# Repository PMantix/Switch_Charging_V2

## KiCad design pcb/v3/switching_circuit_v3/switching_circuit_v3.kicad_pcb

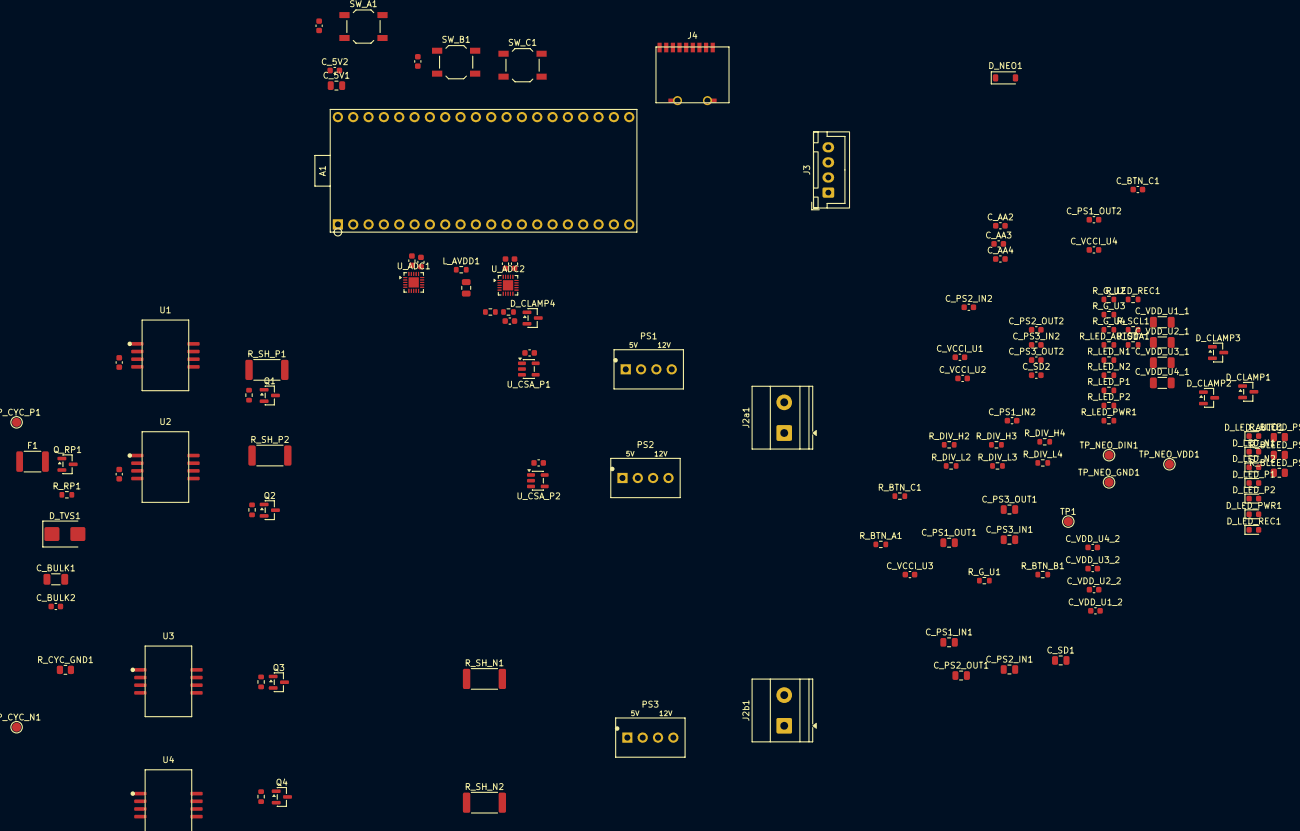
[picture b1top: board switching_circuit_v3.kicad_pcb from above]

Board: 2 copper layers, 128 parts (0 on the bottom side), 70 nets, no tracks yet.

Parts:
A1: Pico2; Pico2_SocketedTH
C_5V1: 10uF; C_0805_2012Metric
C_5V2: 100nF; C_0603_1608Metric
C_AA1, C_AA2, C_AA3, C_AA4: 100nF; C_0603_1608Metric
C_AVDD1: 10uF; C_0805_2012Metric
C_AVDD2_U1, C_AVDD2_U2: 100nF; C_0603_1608Metric
C_BTN_A1: 100nF; C_0603_1608Metric
C_BTN_B1: 100nF; C_0603_1608Metric
C_BTN_C1: 100nF; C_0603_1608Metric
C_BULK1: 10uF; C_1206_3216Metric
C_BULK2: 100nF; C_0603_1608Metric
C_CAP_U1, C_CAP_U2: 220nF; C_0603_1608Metric
C_CSA_P1, C_CSA_P2: 100nF; C_0603_1608Metric
C_DVDD_U1, C_DVDD_U2: 1uF; C_0603_1608Metric
C_PS1_IN1, C_PS2_IN1, C_PS3_IN1: 4.7uF; C_0805_2012Metric
C_PS1_IN2, C_PS1_OUT2, C_PS2_IN2, C_PS2_OUT2, C_PS3_IN2, C_PS3_OUT2: 100nF; C_0603_1608Metric
C_PS1_OUT1, C_PS2_OUT1, C_PS3_OUT1: 2.2uF; C_0805_2012Metric
C_SD1: 10uF; C_0805_2012Metric
C_SD2: 100nF; C_0603_1608Metric
C_VCCI_U1, C_VCCI_U2, C_VCCI_U3, C_VCCI_U4: 100nF; C_0603_1608Metric
C_VDD_U1_1, C_VDD_U2_1, C_VDD_U3_1, C_VDD_U4_1: 10uF; C_1206_3216Metric
C_VDD_U1_2, C_VDD_U2_2, C_VDD_U3_2, C_VDD_U4_2: 100nF; C_0603_1608Metric
D_CLAMP1, D_CLAMP2, D_CLAMP3, D_CLAMP4: BAV99; SOT-23
D_LED_AUTO1: YELLOW; LED_0603_1608Metric
D_LED_N1, D_LED_N2: GREEN; LED_0603_1608Metric
D_LED_P1, D_LED_P2: GREEN; LED_0603_1608Metric
D_LED_PWR1: GREEN; LED_0603_1608Metric
D_LED_REC1: GREEN; LED_0603_1608Metric
D_NEO1: 1N4148W; D_SOD-123
D_TVS1: SMBJ12CA; D_SMB
F1: 3A; Fuse_1812_4532Metric
J2a1: Cell+; TerminalBlock_Phoenix_MKDS-1,5-2-5.08_1x02_P5.08mm_Horizont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
J2b1: Cell-; TerminalBlock_Phoenix_MKDS-1,5-2-5.08_1x02_P5.08mm_Horizont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
J3: OLED; JST_XH_B4B-XH-A_1x04_P2.50mm_Vertical
J4: microSD; TF_PUSH
L_AVDD1: 600R@100MHz; R_0603_1608Metric
PS1, PS2, PS3: B0512S-1WR3; B0512S_1WR3_SIP4
Q1, Q2, Q3, Q4: AO3400A; SOT-23
Q_RP1: AO3401A; SOT-23
R_BLEED_PS1, R_BLEED_PS2, R_BLEED_PS3: 1.2k; R_0805_2012Metric
R_BTN_A1: 10k; R_0603_1608Metric
R_BTN_B1: 10k; R_0603_1608Metric
R_BTN_C1: 10k; R_0603_1608Metric
R_CYC_GND1: 0R; R_0805_2012Metric
R_DIV_H1, R_DIV_H2, R_DIV_H3, R_DIV_H4: 91k; R_0603_1608Metric
R_DIV_L1, R_DIV_L2, R_DIV_L3, R_DIV_L4: 9.1k; R_0603_1608Metric
R_G_U1, R_G_U2, R_G_U3, R_G_U4: 10R; R_0603_1608Metric
R_LED_AUTO1: 1k; R_0603_1608Metric
R_LED_N1, R_LED_N2: 1k; R_0603_1608Metric
R_LED_P1, R_LED_P2: 1k; R_0603_1608Metric
R_LED_PWR1: 1k; R_0603_1608Metric
R_LED_REC1: 1k; R_0603_1608Metric
R_RP1: 10k; R_0603_1608Metric
R_SCL1: 4.7k; R_0603_1608Metric
R_SDA1: 4.7k; R_0603_1608Metric
R_SH_N1, R_SH_N2: 0R01; R_2512_6332Metric
R_SH_P1, R_SH_P2: 0R01; R_2512_6332Metric
Rgpd_1, Rgpd_2, Rgpd_3, Rgpd_4: 10k; R_0603_1608Metric
SW_A1: SW; SW_SPST_TL3342
SW_B1: SW; SW_SPST_TL3342
SW_C1: SW; SW_SPST_TL3342
TP1: GP28; TestPoint_Pad_D1.5mm
TP_CYC_N1: CYCLER_IN-; TestPoint_Pad_D1.5mm
TP_CYC_P1: CYCLER_IN+; TestPoint_Pad_D1.5mm
TP_NEO_DIN1: NEO_DIN; TestPoint_Pad_D1.5mm
TP_NEO_GND1: NEO_GND; TestPoint_Pad_D1.5mm
TP_NEO_VDD1: NEO_VDD; TestPoint_Pad_D1.5mm
U1, U2, U3, U4: UCC5304DWVR; SOIC-8_DWV_7.5x11.5mm_P1.27mm
U_ADC1, U_ADC2: ADS131M04; Texas_RUK0020B_WQFN-20-1EP_3x3mm_P0.4mm_EP1.7x1.7mm
U_CSA_P1, U_CSA_P2: INA180A1; SOT-23-5

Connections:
+3V3: A1.3V3_OUT, C_CSA_P1.1, C_CSA_P2.1, C_DVDD_U1.1, C_DVDD_U2.1, C_SD1.1, C_SD2.1, C_VCCI_U1.1, C_VCCI_U2.1, C_VCCI_U3.1, C_VCCI_U4.1, D_LED_N1.2 (A), D_LED_N2.2 (A), D_LED_P1.2 (A), D_LED_P2.2 (A), D_LED_PWR1.2 (A), J3.1, J4.5, L_AVDD1.1, R_BTN_A1.1, R_BTN_B1.1, R_BTN_C1.1, R_SCL1.1, R_SDA1.1, U1.2 (VCCI), U1.3 (VCCI), U2.2 (VCCI), U2.3 (VCCI), U3.2 (VCCI), U3.3 (VCCI), U4.2 (VCCI), U4.3 (VCCI), U_ADC1.18 (DVDD), U_ADC2.18 (DVDD), U_CSA_P1.5 (VS), U_CSA_P2.5 (VS)
+3V3_A: C_AVDD1.1, C_AVDD2_U1.1, C_AVDD2_U2.1, D_CLAMP1.2 (S), D_CLAMP2.2 (S), D_CLAMP3.2 (S), D_CLAMP4.2 (S), L_AVDD1.2, U_ADC1.19 (AVDD), U_ADC2.19 (AVDD)
+5V: A1.VBUS, C_5V1.1, C_5V2.1, C_PS1_IN1.1, C_PS1_IN2.1, C_PS2_IN1.1, C_PS2_IN2.1, C_PS3_IN1.1, C_PS3_IN2.1, D_NEO1.2 (A), PS1.2 (Vin+), PS2.2 (Vin+), PS3.2 (Vin+)
+HV: C_BULK1.1, C_BULK2.1, D_TVS1.2 (A2), Q_RP1.3 (D), R_DIV_H1.1, R_SH_P1.1, R_SH_P2.1, U_CSA_P1.3 (IN+), U_CSA_P2.3 (IN+)
+HV_P1: Q1.3 (D), R_DIV_H2.1, R_SH_P1.2, U_CSA_P1.4 (IN-)
+HV_P2: Q2.3 (D), R_DIV_H3.1, R_SH_P2.2, U_CSA_P2.4 (IN-)
+HV_PREFUSE: F1.2, Q_RP1.2 (S), R_RP1.1
ADS1_CS: A1.GP13, U_ADC1.10 (CS)
ADS1_DRDY: A1.GP14, U_ADC1.11 (DRDY)
ADS2_CS: A1.GP26, U_ADC2.10 (CS)
ADS2_DRDY: A1.GP21, U_ADC2.11 (DRDY)
ADS_CLKIN: A1.GP27, U_ADC1.15 (CLKIN), U_ADC2.15 (CLKIN)
ADS_MISO: A1.GP12, U_ADC1.13 (DOUT), U_ADC2.13 (DOUT)
ADS_MOSI: A1.GP11, U_ADC1.14 (DIN), U_ADC2.14 (DIN)
ADS_RESET: A1.GP15, U_ADC1.9 (SYNC/RESET), U_ADC2.9 (SYNC/RESET)
ADS_SCK: A1.GP10, U_ADC1.12 (SCLK), U_ADC2.12 (SCLK)
AGND: A1.AGND, C_AA1.2, C_AA2.2, C_AA3.2, C_AA4.2, C_AVDD1.2, C_AVDD2_U1.2, C_AVDD2_U2.2, D_CLAMP1.1 (G), D_CLAMP2.1 (G), D_CLAMP3.1 (G), D_CLAMP4.1 (G), R_DIV_L1.2, R_DIV_L2.2, R_DIV_L3.2, R_DIV_L4.2, U_ADC1.2 (AIN0N), U_ADC1.3 (AIN1N), U_ADC1.20 (AGND), U_ADC1.21 (EPAD), U_ADC2.2 (AIN0N), U_ADC2.3 (AIN1N), U_ADC2.6 (AIN2N), U_ADC2.7 (AIN3N), U_ADC2.20 (AGND), U_ADC2.21 (EPAD)
BTN_A: A1.GP8, C_BTN_A1.1, R_BTN_A1.2, SW_A1.1
BTN_B: A1.GP9, C_BTN_B1.1, R_BTN_B1.2, SW_B1.1
BTN_C: A1.GP20, C_BTN_C1.1, R_BTN_C1.2, SW_C1.1
CAP1: C_CAP_U1.1, U_ADC1.16 (CAP)
CAP2: C_CAP_U2.1, U_ADC2.16 (CAP)
CELL_A_NEG: J2b1.1, Q3.3 (D)
CELL_A_POS: C_PS1_OUT1.2, C_PS1_OUT2.2, C_VDD_U1_1.2, C_VDD_U1_2.2, J2a1.1, PS1.3 (Vout-), Q1.2 (S), R_BLEED_PS1.2, Rgpd_1.2, U1.5 (VSS), U1.6 (VSS)
CELL_B_NEG: J2b1.2, Q4.3 (D)
CELL_B_POS: C_PS2_OUT1.2, C_PS2_OUT2.2, C_VDD_U2_1.2, C_VDD_U2_2.2, J2a1.2, PS2.3 (Vout-), Q2.2 (S), R_BLEED_PS2.2, Rgpd_2.2, U2.5 (VSS), U2.6 (VSS)
CSA_P1_OUT: U_ADC1.1 (AIN0P), U_CSA_P1.1 (OUT)
CSA_P2_OUT: U_ADC1.4 (AIN1P), U_CSA_P2.1 (OUT)
CYCLER_IN+: F1.1, TP_CYC_P1.1 (1_1)
CYCLER_IN-: Q_RP1.1 (G), R_CYC_GND1.1, R_RP1.2, TP_CYC_N1.1 (1_1)
D_LED_N1_K: D_LED_N1.1 (K), R_LED_N1.1
D_LED_N2_K: D_LED_N2.1 (K), R_LED_N2.1
D_LED_P1_K: D_LED_P1.1 (K), R_LED_P1.1
D_LED_P2_K: D_LED_P2.1 (K), R_LED_P2.1
GATE_N1_IN: A1.GP4, R_LED_N1.2, U3.1 (IN)
GATE_N1_OUT: Q3.1 (G), R_G_U3.2, Rgpd_3.1
GATE_N1_OUT_PRE: R_G_U3.1, U3.7 (OUT)
GATE_N2_IN: A1.GP5, R_LED_N2.2, U4.1 (IN)
GATE_N2_OUT: Q4.1 (G), R_G_U4.2, Rgpd_4.1
GATE_N2_OUT_PRE: R_G_U4.1, U4.7 (OUT)
GATE_P1_IN: A1.GP2, R_LED_P1.2, U1.1 (IN)
GATE_P1_OUT: Q1.1 (G), R_G_U1.2, Rgpd_1.1
GATE_P1_OUT_PRE: R_G_U1.1, U1.7 (OUT)
GATE_P2_IN: A1.GP3, R_LED_P2.2, U2.1 (IN)
GATE_P2_OUT: Q2.1 (G), R_G_U2.2, Rgpd_2.1
GATE_P2_OUT_PRE: R_G_U2.1, U2.7 (OUT)
GND: A1.GND1 (GND), A1.GND2 (GND), C_5V1.2, C_5V2.2, C_BTN_A1.2, C_BTN_B1.2, C_BTN_C1.2, C_BULK1.2, C_BULK2.2, C_CAP_U1.2, C_CAP_U2.2, C_CSA_P1.2, C_CSA_P2.2, C_DVDD_U1.2, C_DVDD_U2.2, C_PS1_IN1.2, C_PS1_IN2.2, C_PS2_IN1.2, C_PS2_IN2.2, C_PS3_IN1.2, C_PS3_IN2.2, C_PS3_OUT1.2, C_PS3_OUT2.2, C_SD1.2, C_SD2.2, C_VCCI_U1.2, C_VCCI_U2.2, C_VCCI_U3.2, C_VCCI_U4.2, C_VDD_U3_1.2, C_VDD_U3_2.2, C_VDD_U4_1.2, C_VDD_U4_2.2, D_LED_AUTO1.1 (K), D_LED_REC1.1 (K), D_TVS1.1 (A1), J3.2, J4.6, PS1.1 (Vin-), PS2.1 (Vin-), PS3.1 (Vin-), PS3.3 (Vout-), R_BLEED_PS3.2, R_CYC_GND1.2, R_LED_PWR1.2, R_SH_N1.2, R_SH_N2.2, SW_A1.2, SW_B1.2, SW_C1.2, TP_NEO_GND1.1 (1_1), U1.4 (GND), U2.4 (GND), U3.4 (GND), U3.5 (VSS), U3.6 (VSS), U4.4 (GND), U4.5 (VSS), U4.6 (VSS), U_ADC1.6 (AIN2N), U_ADC1.7 (AIN3N), U_ADC1.17 (DGND), U_ADC2.17 (DGND), U_CSA_P1.2 (GND), U_CSA_P2.2 (GND)
GND_N1: Q3.2 (S), R_DIV_H4.1, R_SH_N1.1, Rgpd_3.2, U_ADC1.5 (AIN2P)
GND_N2: Q4.2 (S), R_SH_N2.1, Rgpd_4.2, U_ADC1.8 (AIN3P)
LED_AUTO: A1.GP0, R_LED_AUTO1.2
LED_AUTO_A: D_LED_AUTO1.2 (A), R_LED_AUTO1.1
LED_REC: A1.GP22, R_LED_REC1.2
LED_REC_A: D_LED_REC1.2 (A), R_LED_REC1.1
NEOPIXEL: A1.GP1, TP_NEO_DIN1.1 (1_1)
NEO_VDD: D_NEO1.1 (K), TP_NEO_VDD1.1 (1_1)
PWR_LED_K: D_LED_PWR1.1 (K), R_LED_PWR1.1
SCL: A1.GP7, J3.4, R_SCL1.2
SDA: A1.GP6, J3.3, R_SDA1.2
SD_CS: A1.GP17, J4.2
SD_MISO: A1.GP16, J4.1
SD_MOSI: A1.GP19, J4.4
SD_SCK: A1.GP18, J4.3
TP_GP28: A1.GP28, TP1.1 (1_1)
VCC2_LS: C_PS3_OUT1.1, C_PS3_OUT2.1, C_VDD_U3_1.1, C_VDD_U3_2.1, C_VDD_U4_1.1, C_VDD_U4_2.1, PS3.4 (Vout+), R_BLEED_PS3.1, U3.8 (VDD), U4.8 (VDD)
VCC2_P1: C_PS1_OUT1.1, C_PS1_OUT2.1, C_VDD_U1_1.1, C_VDD_U1_2.1, PS1.4 (Vout+), R_BLEED_PS1.1, U1.8 (VDD)
VCC2_P2: C_PS2_OUT1.1, C_PS2_OUT2.1, C_VDD_U2_1.1, C_VDD_U2_2.1, PS2.4 (Vout+), R_BLEED_PS2.1, U2.8 (VDD)
VDIV_GND_N1: C_AA4.1, D_CLAMP4.3 (D), R_DIV_H4.2, R_DIV_L4.1, U_ADC2.8 (AIN3P)
VDIV_HV: C_AA1.1, D_CLAMP1.3 (D), R_DIV_H1.2, R_DIV_L1.1, U_ADC2.1 (AIN0P)
VDIV_HV_P1: C_AA2.1, D_CLAMP2.3 (D), R_DIV_H2.2, R_DIV_L2.1, U_ADC2.4 (AIN1P)
VDIV_HV_P2: C_AA3.1, D_CLAMP3.3 (D), R_DIV_H3.2, R_DIV_L3.1, U_ADC2.5 (AIN2P)

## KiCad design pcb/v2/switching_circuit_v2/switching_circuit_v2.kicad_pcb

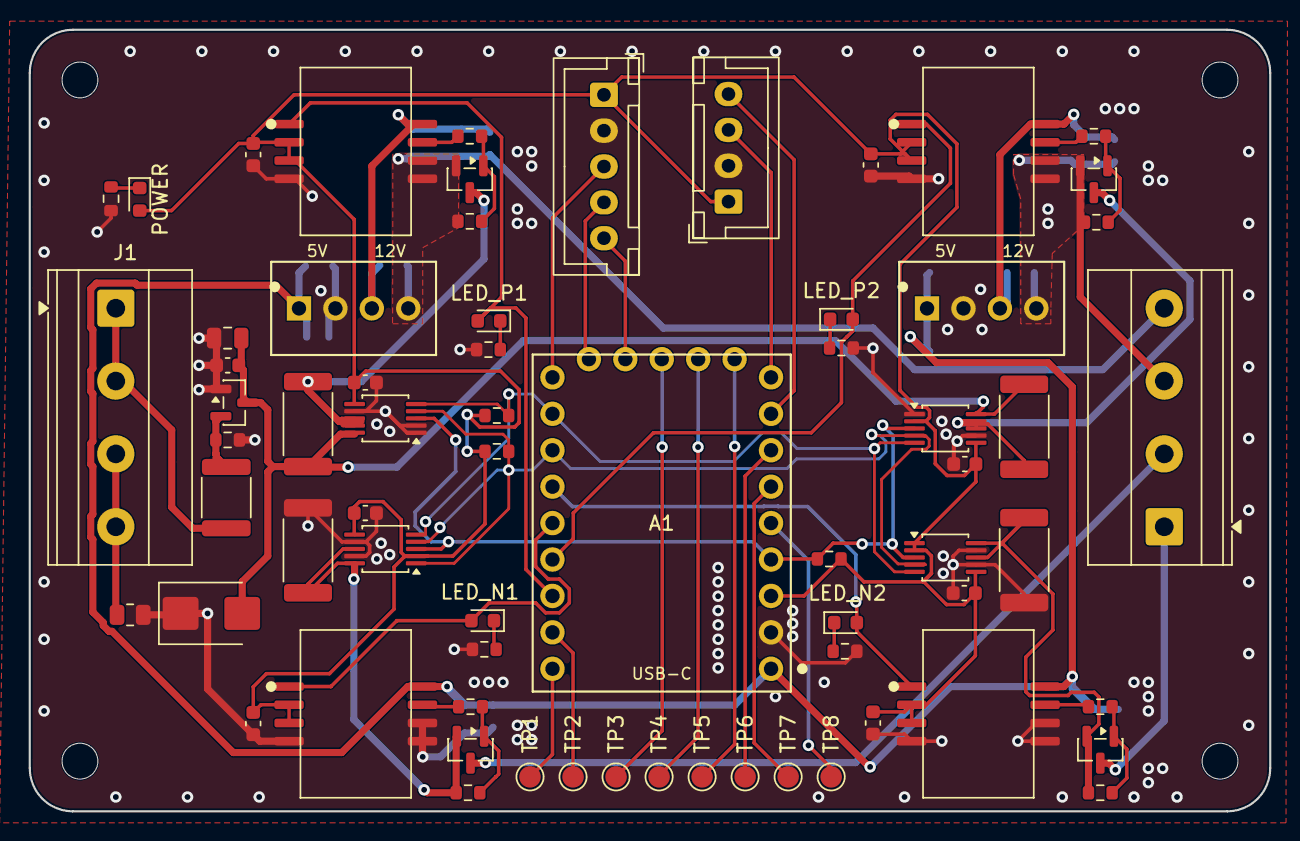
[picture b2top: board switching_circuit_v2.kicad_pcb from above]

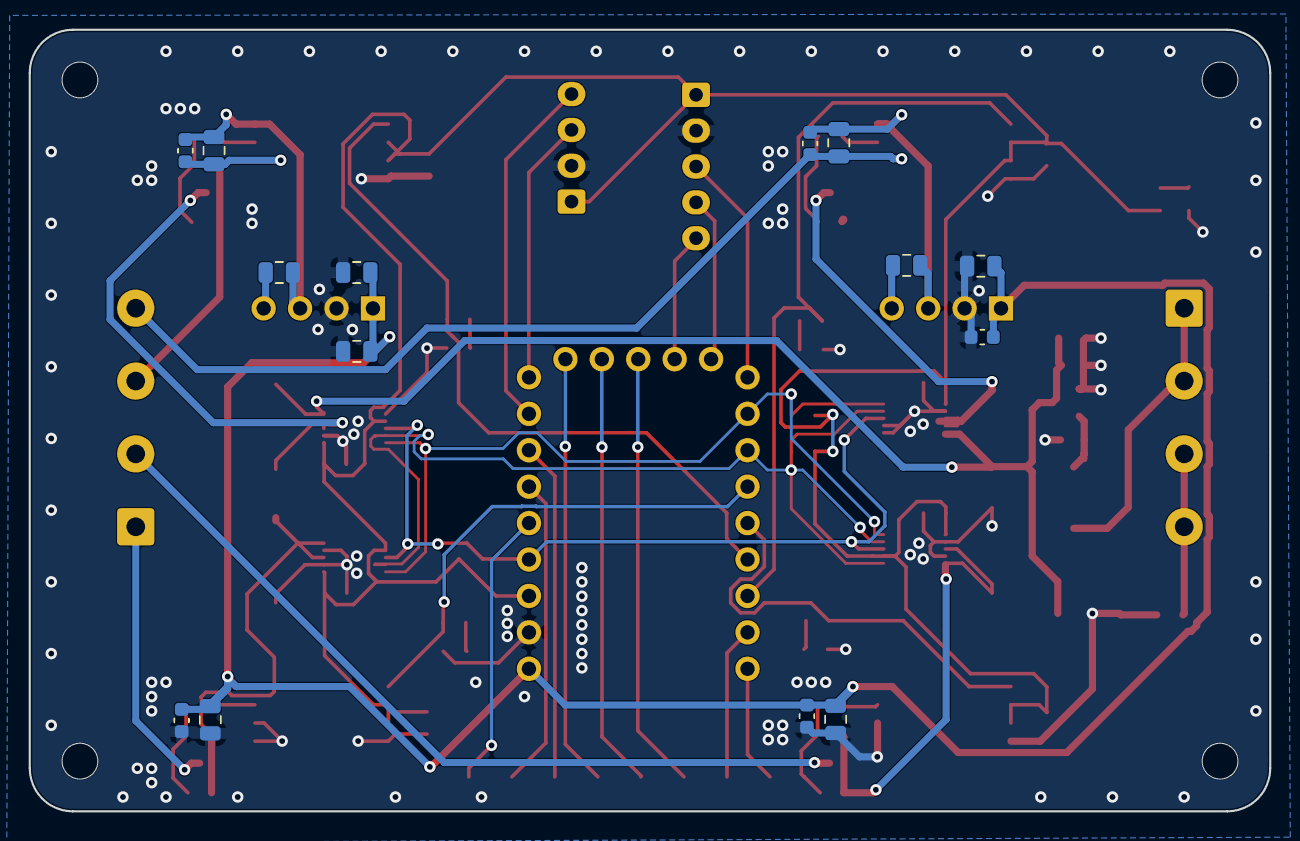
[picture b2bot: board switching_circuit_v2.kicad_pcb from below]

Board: 2 copper layers, 86.5 x 54.5 mm, 81 parts (14 on the bottom side), 50 nets.

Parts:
A1: RP2040-Zero; RP2040_Zero_SocketedTH
C_5V1: 10uF; C_0805_2012Metric
C_5V2: 100nF; C_0603_1608Metric
C_B1: 10uF; C_0805_2012Metric
C_B2: 100nF; C_0603_1608Metric
C_INA_N1, C_INA_N2: 100nF; C_0603_1608Metric
C_INA_P1, C_INA_P2: 100nF; C_0603_1608Metric
C_PS1_IN1, C_PS2_IN1: 4.7uF; C_0805_2012Metric
C_PS1_OUT1, C_PS2_OUT1: 2.2uF; C_0805_2012Metric
C_VCCI_U1, C_VCCI_U2, C_VCCI_U3, C_VCCI_U4: 100nF; C_0603_1608Metric
C_VDD_U1_1, C_VDD_U2_1, C_VDD_U3_1, C_VDD_U4_1: 10uF; C_0805_2012Metric
C_VDD_U1_2, C_VDD_U2_2, C_VDD_U3_2, C_VDD_U4_2: 100nF; C_0603_1608Metric
D_LED_N1: GREEN; LED_0603_1608Metric
D_TVS1: SMBJ12CA; D_SMB
F1: 3A; Fuse_1812_4532Metric
J1: Cycler In; TerminalBlock_Phoenix_MKDS-1,5-4-5.08_1x04_P5.08mm_Horizont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
J2: Cell; TerminalBlock_Phoenix_MKDS-1,5-4-5.08_1x04_P5.08mm_Horizont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
J3: Encoder; JST_XH_B5B-XH-A_1x05_P2.50mm_Vertical
J4: Display; JST_XH_B4B-XH-A_1x04_P2.50mm_Vertical
LED_N1: 1k; R_0603_1608Metric
LED_N2: GREEN; LED_0603_1608Metric
LED_P1, LED_P2: GREEN; LED_0603_1608Metric
POWER: GREEN; LED_0603_1608Metric
PS1, PS2: B0512S-1WR3; B0512S_1WR3_SIP4
Q1, Q2, Q3, Q4: AO3400A; SOT-23
Q_RP1: AO3401A; SOT-23
R_ALERT1: 4.7k; R_0603_1608Metric
R_CYC_GND1: 0R; R_0805_2012Metric
R_G_U1, R_G_U2, R_G_U3, R_G_U4: 10R; R_0603_1608Metric
R_LED_N2: 1k; R_0603_1608Metric
R_LED_P1, R_LED_P2: 1k; R_0603_1608Metric
R_LED_PWR1: 1k; R_0603_1608Metric
R_RP1: 10k; R_0603_1608Metric
R_SCL1: 4.7k; R_0603_1608Metric
R_SDA1: 4.7k; R_0603_1608Metric
R_SH_N1, R_SH_N2: 0R05; R_2512_6332Metric
R_SH_P1, R_SH_P2: 0R05; R_2512_6332Metric
Rgpd_1, Rgpd_2, Rgpd_3, Rgpd_4: 10k; R_0603_1608Metric
TP1: TP TP_GP0; TestPoint_Pad_D1.5mm
TP2: TP TP_GP1; TestPoint_Pad_D1.5mm
TP3: TP TP_GP11; TestPoint_Pad_D1.5mm
TP4: TP TP_GP12; TestPoint_Pad_D1.5mm
TP5: TP TP_GP13; TestPoint_Pad_D1.5mm
TP6: TP TP_GP26; TestPoint_Pad_D1.5mm
TP7: TP TP_GP27; TestPoint_Pad_D1.5mm
TP8: TP TP_GP28; TestPoint_Pad_D1.5mm
U1, U2, U3, U4: UCC5304DWVR; SOIC-8_DWV_7.5x11.5mm_P1.27mm
U_INA_N1, U_INA_N2: INA226; TSSOP-10_3x3mm_P0.5mm
U_INA_P1, U_INA_P2: INA226; TSSOP-10_3x3mm_P0.5mm

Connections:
+3V3: A1.3V3, C_INA_N1.1, C_INA_N2.1, C_INA_P1.1, C_INA_P2.1, C_VCCI_U1.1, C_VCCI_U2.1, C_VCCI_U3.1, C_VCCI_U4.1, J3.1, J4.1, POWER.2 (A), R_ALERT1.1, R_SCL1.1, R_SDA1.1, U1.2 (VCCI), U1.3 (VCCI), U2.2 (VCCI), U2.3 (VCCI), U3.2 (VCCI), U3.3 (VCCI), U4.2 (VCCI), U4.3 (VCCI), U_INA_N1.2 (A0), U_INA_N1.6 (VS), U_INA_N2.1 (A1), U_INA_N2.2 (A0), U_INA_N2.6 (VS), U_INA_P1.6 (VS), U_INA_P2.2 (A0), U_INA_P2.6 (VS)
+5V: A1.5V, C_5V1.1, C_5V2.1, C_PS1_IN1.1, C_PS2_IN1.1, C_VDD_U3_1.1, C_VDD_U3_2.1, C_VDD_U4_1.1, C_VDD_U4_2.1, PS1.1 (Vin+), PS2.1 (Vin+), U3.8 (VDD), U4.8 (VDD)
+HV: C_B1.1, C_B2.1, D_TVS1.2 (A2), Q_RP1.3 (D), R_SH_P1.1, R_SH_P2.1, U_INA_P1.10 (Vin+), U_INA_P2.10 (Vin+)
+HV_P1: Q1.3 (D), R_SH_P1.2, U_INA_P1.8 (Vbus), U_INA_P1.9 (Vin-)
+HV_P2: Q2.3 (D), R_SH_P2.2, U_INA_P2.8 (Vbus), U_INA_P2.9 (Vin-)
+HV_PREFUSE: F1.2, Q_RP1.2 (S), R_RP1.1
ALERT: A1.GP29, R_ALERT1.2, U_INA_N1.3 (~Alert), U_INA_N2.3 (~Alert), U_INA_P1.3 (~Alert), U_INA_P2.3 (~Alert)
CELL_A_NEG: J2.2, Q3.3 (D)
CELL_A_POS: C_PS1_OUT1.2, C_VDD_U1_1.2, C_VDD_U1_2.2, J2.4, PS1.4 (Vout-), Q1.2 (S), Rgpd_1.2, U1.5 (VSS), U1.6 (VSS)
CELL_B_NEG: J2.1, Q4.3 (D)
CELL_B_POS: C_PS2_OUT1.2, C_VDD_U2_1.2, C_VDD_U2_2.2, J2.3, PS2.4 (Vout-), Q2.2 (S), Rgpd_2.2, U2.5 (VSS), U2.6 (VSS)
CYCLER_IN+: F1.1, J1.1, J1.2
CYCLER_IN-: J1.3, J1.4, R_CYC_GND1.1
DISPLAY_CLK: A1.GP14, J4.3
DISPLAY_DIO: A1.GP15, J4.4
D_LED_N1_K: D_LED_N1.1 (K), LED_N1.1
D_LED_N2_K: LED_N2.1 (K), R_LED_N2.1
D_LED_P1_K: LED_P1.1 (K), R_LED_P1.1
D_LED_P2_K: LED_P2.1 (K), R_LED_P2.1
ENC_CLK: A1.GP8, J3.3
ENC_DT: A1.GP9, J3.4
ENC_SW: A1.GP10, J3.5
GATE_N1_IN: A1.GP4, D_LED_N1.2 (A), U3.1 (IN)
GATE_N1_OUT: Q3.1 (G), R_G_U3.2, Rgpd_3.1
GATE_N1_OUT_PRE: R_G_U3.1, U3.7 (OUT)
GATE_N2_IN: A1.GP5, LED_N2.2 (A), U4.1 (IN)
GATE_N2_OUT: Q4.1 (G), R_G_U4.2, Rgpd_4.1
GATE_N2_OUT_PRE: R_G_U4.1, U4.7 (OUT)
GATE_P1_IN: A1.GP2, LED_P1.2 (A), U1.1 (IN)
GATE_P1_OUT: Q1.1 (G), R_G_U1.2, Rgpd_1.1
GATE_P1_OUT_PRE: R_G_U1.1, U1.7 (OUT)
GATE_P2_IN: A1.GP3, LED_P2.2 (A), U2.1 (IN)
GATE_P2_OUT: Q2.1 (G), R_G_U2.2, Rgpd_2.1
GATE_P2_OUT_PRE: R_G_U2.1, U2.7 (OUT)
GND: A1.GND, C_5V1.2, C_5V2.2, C_B1.2, C_B2.2, C_INA_N1.2, C_INA_N2.2, C_INA_P1.2, C_INA_P2.2, C_PS1_IN1.2, C_PS2_IN1.2, C_VCCI_U1.2, C_VCCI_U2.2, C_VCCI_U3.2, C_VCCI_U4.2, C_VDD_U3_1.2, C_VDD_U3_2.2, C_VDD_U4_1.2, C_VDD_U4_2.2, D_TVS1.1 (A1), J3.2, J4.2, LED_N1.2, PS1.2 (Vin-), PS2.2 (Vin-), Q_RP1.1 (G), R_CYC_GND1.2, R_LED_N2.2, R_LED_P1.2, R_LED_P2.2, R_LED_PWR1.2, R_RP1.2, R_SH_N1.2, R_SH_N2.2, U1.4 (GND), U2.4 (GND), U3.4 (GND), U3.5 (VSS), U3.6 (VSS), U4.4 (GND), U4.5 (VSS), U4.6 (VSS), U_INA_N1.7 (GND), U_INA_N1.9 (Vin-), U_INA_N2.7 (GND), U_INA_N2.9 (Vin-), U_INA_P1.1 (A1), U_INA_P1.2 (A0), U_INA_P1.7 (GND), U_INA_P2.1 (A1), U_INA_P2.7 (GND)
GND_N1: Q3.2 (S), R_SH_N1.1, Rgpd_3.2, U_INA_N1.8 (Vbus), U_INA_N1.10 (Vin+)
GND_N2: Q4.2 (S), R_SH_N2.1, Rgpd_4.2, U_INA_N2.8 (Vbus), U_INA_N2.10 (Vin+)
PWR_LED_K: POWER.1 (K), R_LED_PWR1.1
SCL: A1.GP7, R_SCL1.2, U_INA_N1.5 (SCL), U_INA_N2.5 (SCL), U_INA_P1.5 (SCL), U_INA_P2.5 (SCL)
SDA: A1.GP6, R_SDA1.2, U_INA_N1.1 (A1), U_INA_N1.4 (SDA), U_INA_N2.4 (SDA), U_INA_P1.4 (SDA), U_INA_P2.4 (SDA)
TP_GP0: A1.GP0, TP1.1 (1_1)
TP_GP1: A1.GP1, TP2.1 (1_1)
TP_GP11: A1.GP11, TP3.1 (1_1)
TP_GP12: A1.GP12, TP4.1 (1_1)
TP_GP13: A1.GP13, TP5.1 (1_1)
TP_GP26: A1.GP26, TP6.1 (1_1)
TP_GP27: A1.GP27, TP7.1 (1_1)
TP_GP28: A1.GP28, TP8.1 (1_1)
VCC2_P1: C_PS1_OUT1.1, C_VDD_U1_1.1, C_VDD_U1_2.1, PS1.3 (Vout+), U1.8 (VDD)
VCC2_P2: C_PS2_OUT1.1, C_VDD_U2_1.1, C_VDD_U2_2.1, PS2.3 (Vout+), U2.8 (VDD)

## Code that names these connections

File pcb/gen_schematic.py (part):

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        (60, 80),
        value="AO3400A",
        footprint="Package_TO_SOT_SMD:SOT-23",
        pin_nets={"1": "GATE_P1_OUT", "2": "CELL_A_POS", "3": "+HV_P1"},
        fields={"MPN": "AO3400A", "LCSC": "C20917"},
    )
)
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        (120, 80),
        value="AO3400A",
        footprint="Package_TO_SOT_SMD:SOT-23",
        pin_nets={"1": "GATE_P2_OUT", "2": "CELL_B_POS", "3": "+HV_P2"},
        fields={"MPN": "AO3400A", "LCSC": "C20917"},
    )
)
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        (60, 130),
        value="AO3400A",
        footprint="Package_TO_SOT_SMD:SOT-23",
        pin_nets={"1": "GATE_N1_OUT", "2": "GND_N1", "3": "CELL_A_NEG"},
        fields={"MPN": "AO3400A", "LCSC": "C20917"},
    )
)
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        (120, 130),
        value="AO3400A",
        footprint="Package_TO_SOT_SMD:SOT-23",
        pin_nets={"1": "GATE_N2_OUT", "2": "GND_N2", "3": "CELL_B_NEG"},
        fields={"MPN": "AO3400A", "LCSC": "C20917"},
    )
)
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    )

# Cell terminal J2 — 4-pin screw terminal
# Connector:Screw_Terminal_01x04 pin 1 = top, so: 1=CELL_A_POS, 2=CELL_A_NEG, 3=CELL_B_POS, 4=CELL_B_NEG
add(
    Part(
        "J2",
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        (320, 200),
        value="GREEN",
        footprint="LED_SMD:LED_0603_1608Metric",
        pin_nets={"1": "PWR_LED_K", "2": "+3V3"},
    )
)
add(
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        (320, 205),
        value="1k",
        footprint="Resistor_SMD:R_0603_1608Metric",
        pin_nets={"1": "PWR_LED_K", "2": "GND"},
    )
)

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
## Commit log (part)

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2026-04-25 Revert "Switch sensor stream to binary frame format (3.16x throughput)"
    This reverts commit 845c40d629db470fae3800e9635b43253fefd44e.
2026-04-25 Revert "Bump default INA226 bus_every to 5; add runtime CT (U) and mem (E) commands"
    This reverts commit 07ae9a32c0dd21fc98a774da6be56d05c9f97af7.
2026-04-26 TUI: Pi picker — Shift-P to swap active Pi
    Adds a modal that probes all eight pi-SW#.local hostnames in parallel,
    lists live ones with latency (offline ones dimmed), and retargets the
    existing PiClient via reconnect_to. Refuses to switch while a recording
    is active so data isn't silently abandoned.
    - discovery.discover_fleet / FleetHit: full-fleet enumeration
    - widgets/pi_list.PiList: latency-aware list (separate from FleetList
2026-04-26 tests: guard start_switching against None resp in mock mode
    Mock GPIO _send returns None; resp.split() raised AttributeError, breaking
    set_mode("charge") and auto-mode tests. Return (None, None) early so the
    sequence engine's monotonic() fallback kicks in.
